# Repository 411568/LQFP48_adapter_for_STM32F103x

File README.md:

<h2>🧐 Features</h2>

This board was created as a test board for STM32F103x microcontrollers. It allows us to use STM32 uC on breadboards etc. during testing. 

<h2>🛡️ License:</h2>

This project is licensed under the MIT License.

<h2> 🙋‍♂️Authors </h2>

- Krzysztof Sikora

<h2>💖Like my work?</h2>

If you have any questions about the project feel free to contact us via email: krzysieksikora717@gmail.com

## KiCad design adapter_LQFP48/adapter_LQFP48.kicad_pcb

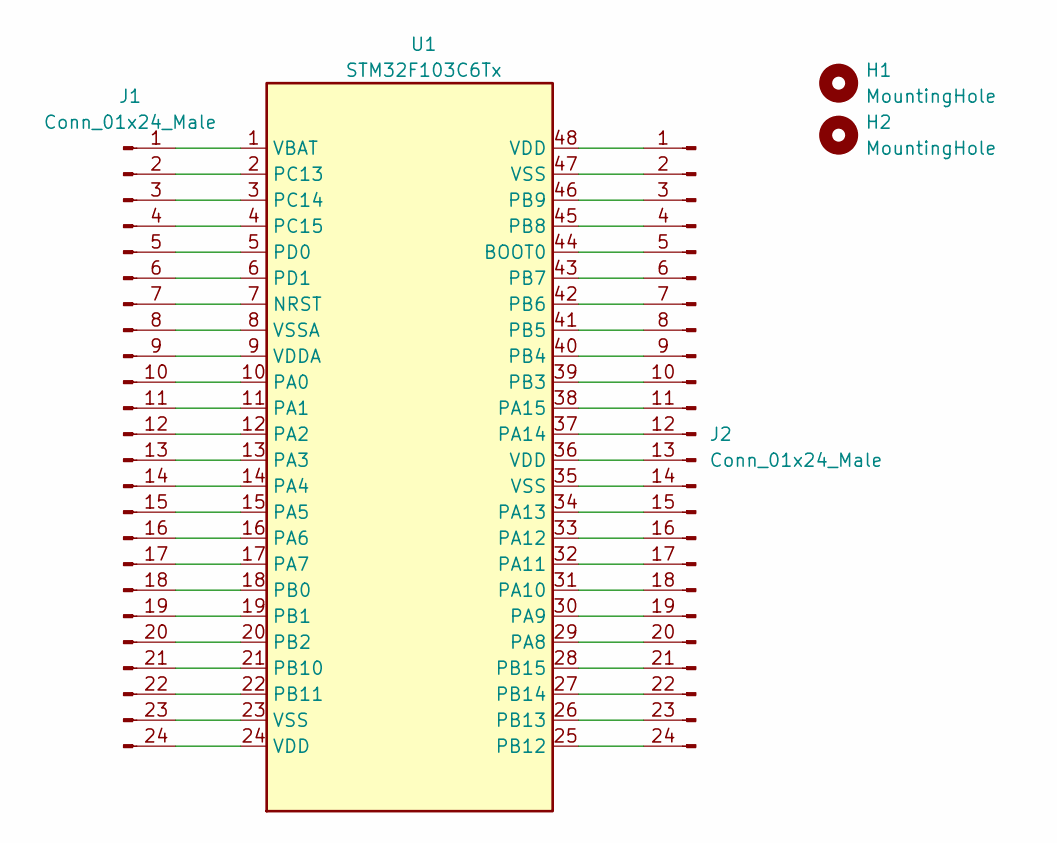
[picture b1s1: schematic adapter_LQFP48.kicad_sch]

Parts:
H1, H2: MountingHole; MountingHole_3.2mm_M3
J1, J2: Conn_01x24_Male; PinHeader_1x24_P2.54mm_Vertical
U1: STM32F103C6Tx; LQFP-48_7x7mm_P0.5mm

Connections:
unnamed: J1.1, U1.1 (VBAT)
unnamed: J1.2, U1.2 (PC13)
unnamed: J1.3, U1.3 (PC14)
unnamed: J1.4, U1.4 (PC15)
unnamed: J1.5, U1.5 (PD0)
unnamed: J1.6, U1.6 (PD1)
unnamed: J1.7, U1.7 (NRST)
unnamed: J1.8, U1.8 (VSSA)
unnamed: J1.9, U1.9 (VDDA)
unnamed: J1.10, U1.10 (PA0)
unnamed: J1.11, U1.11 (PA1)
unnamed: J1.12, U1.12 (PA2)
unnamed: J1.13, U1.13 (PA3)
unnamed: J1.14, U1.14 (PA4)
unnamed: J1.15, U1.15 (PA5)
unnamed: J1.16, U1.16 (PA6)
unnamed: J1.17, U1.17 (PA7)
unnamed: J1.18, U1.18 (PB0)
unnamed: J1.19, U1.19 (PB1)
unnamed: J1.20, U1.20 (PB2)
unnamed: J1.21, U1.21 (PB10)
unnamed: J1.22, U1.22 (PB11)
unnamed: J1.23, U1.23 (VSS)
unnamed: J1.24, U1.24 (VDD)
unnamed: J2.1, U1.48 (VDD)
unnamed: J2.2, U1.47 (VSS)
unnamed: J2.3, U1.46 (PB9)
unnamed: J2.4, U1.45 (PB8)
unnamed: J2.5, U1.44 (BOOT0)
unnamed: J2.6, U1.43 (PB7)
unnamed: J2.7, U1.42 (PB6)
unnamed: J2.8, U1.41 (PB5)
unnamed: J2.9, U1.40 (PB4)
unnamed: J2.10, U1.39 (PB3)
unnamed: J2.11, U1.38 (PA15)
unnamed: J2.12, U1.37 (PA14)
unnamed: J2.13, U1.36 (VDD)
unnamed: J2.14, U1.35 (VSS)
unnamed: J2.15, U1.34 (PA13)
unnamed: J2.16, U1.33 (PA12)
unnamed: J2.17, U1.32 (PA11)
unnamed: J2.18, U1.31 (PA10)
unnamed: J2.19, U1.30 (PA9)
unnamed: J2.20, U1.29 (PA8)
unnamed: J2.21, U1.28 (PB15)
unnamed: J2.22, U1.27 (PB14)
unnamed: J2.23, U1.26 (PB13)
unnamed: J2.24, U1.25 (PB12)

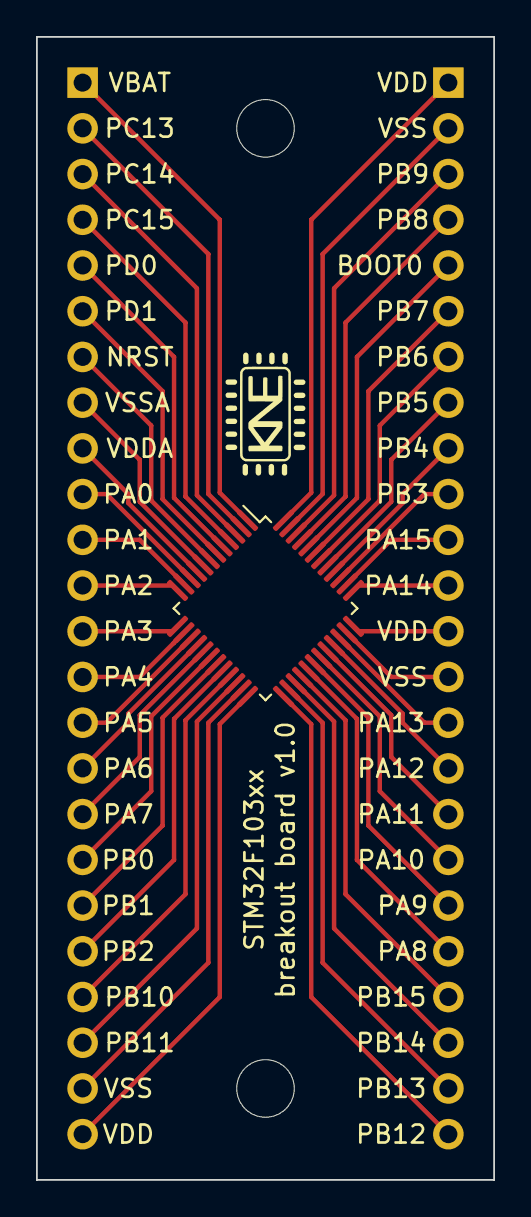
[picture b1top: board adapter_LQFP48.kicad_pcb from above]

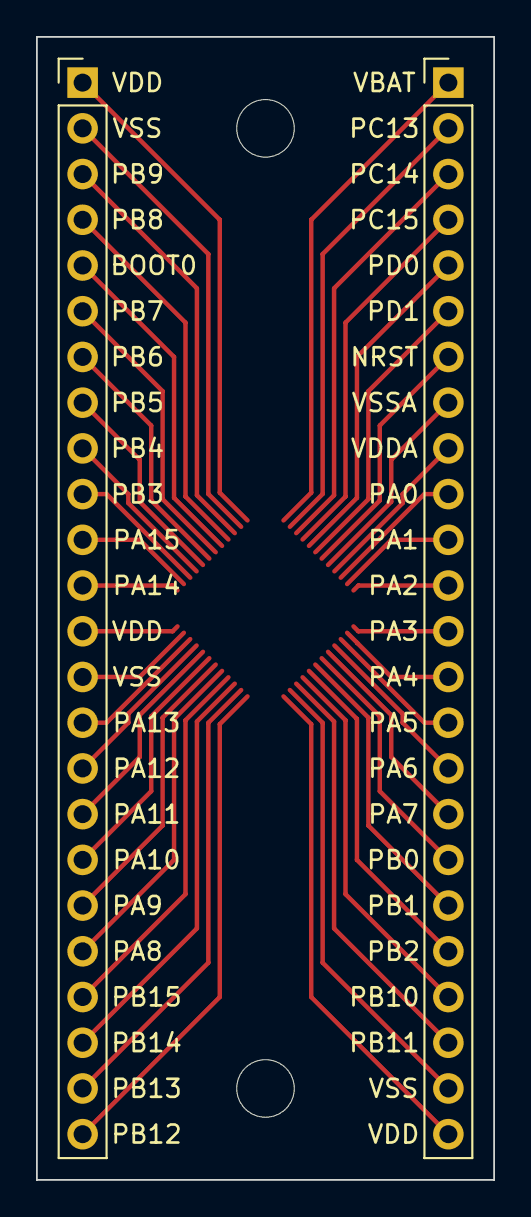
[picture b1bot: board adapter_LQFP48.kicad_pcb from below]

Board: 2 copper layers, 25.4 x 63.5 mm, 5 parts (2 on the bottom side), 48 nets.

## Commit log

2023-01-04 v1_0
2023-01-04 add readme
2025-01-30 Create LICENSE
